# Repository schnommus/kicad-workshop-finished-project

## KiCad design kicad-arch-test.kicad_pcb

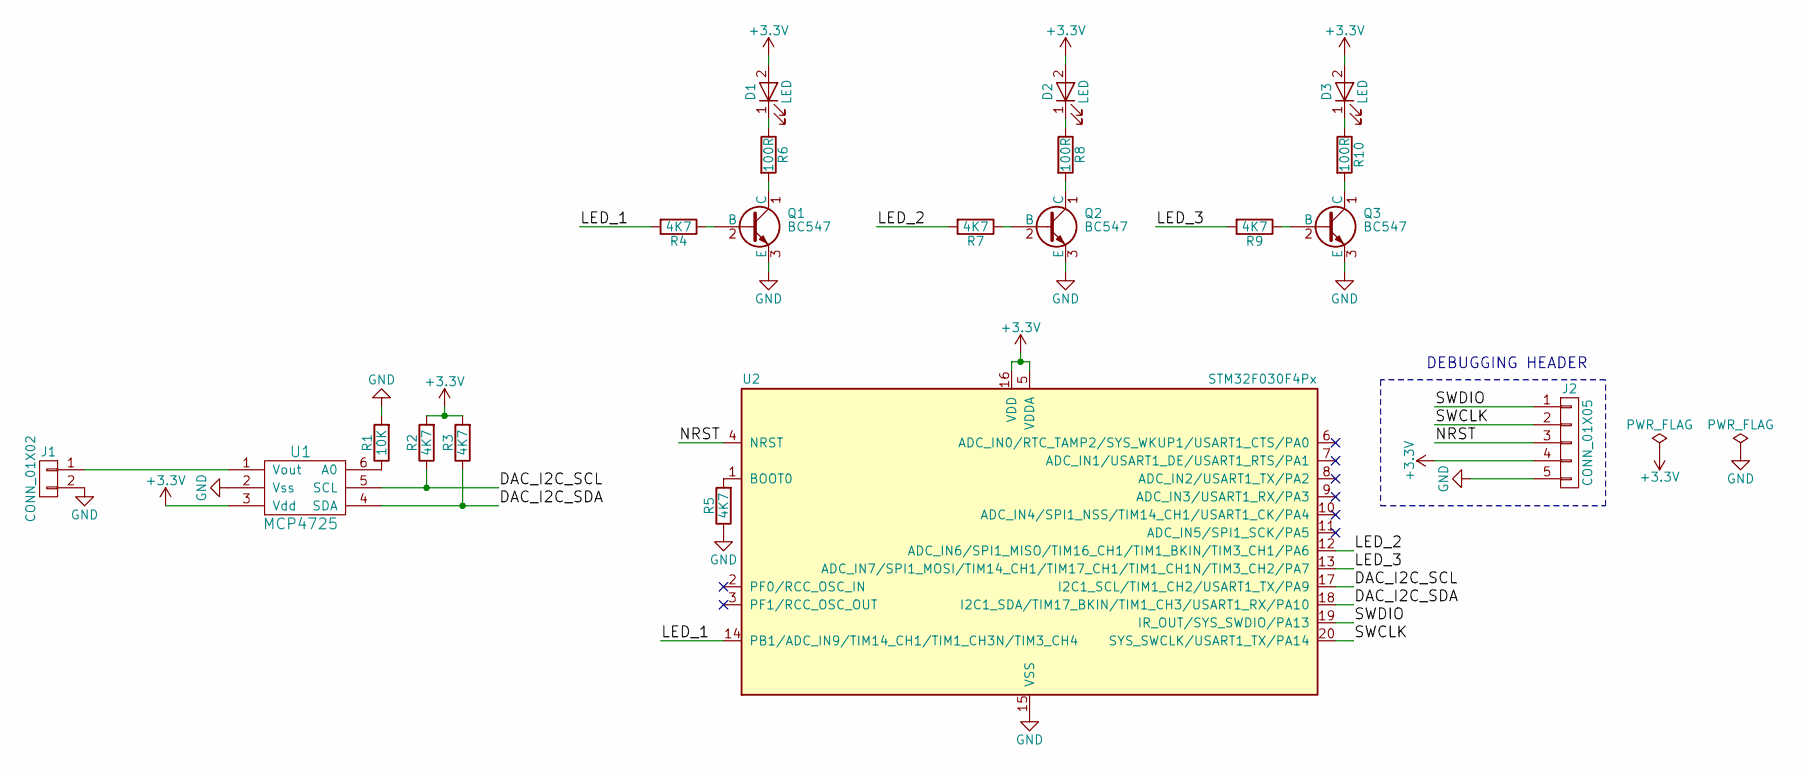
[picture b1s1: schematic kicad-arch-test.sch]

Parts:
D1, D2, D3: LED; LED_0805_HandSoldering
J1: CONN_01X02; Pin_Header_Straight_1x02_Pitch2.54mm
J2: CONN_01X05; Pin_Header_Straight_1x05_Pitch2.54mm
Q1, Q2, Q3: BC547; SOT-23W_Handsoldering
R1: 10K; R_0805_HandSoldering
R2, R3, R4, R5, R7, R9: 4K7; R_0805_HandSoldering
R6, R8, R10: 100R; R_0805_HandSoldering
U1: MCP4725; SOT-23-6_Handsoldering
U2: STM32F030F4Px; TSSOP-20_4.4x6.5mm_Pitch0.65mm

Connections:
+3V3: D1.2 (A), D2.2 (A), D3.2 (A), J2.4, R2.2, R3.2, U1.3 (Vdd), U2.5 (VDDA), U2.16 (VDD)
/DAC_I2C_SCL: R2.1, U1.5 (SCL), U2.17 (I2C1_SCL/TIM1_CH2/USART1_TX/PA9)
/DAC_I2C_SDA: R3.1, U1.4 (SDA), U2.18 (I2C1_SDA/TIM17_BKIN/TIM1_CH3/USART1_RX/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)
/LED_1: R4.2, U2.14 (PB1/ADC_IN9/TIM14_CH1/TIM1_CH3N/TIM3_CH4)
/LED_2: R7.2, U2.12 (ADC_IN6/SPI1_MISO/TIM16_CH1/TIM1_BKIN/T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)
/LED_3: R9.2, U2.13 (ADC_IN7/SPI1_MOSI/TIM14_CH1/TIM17_CH1/T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)
/NRST: J2.3, U2.4 (NRST)
/SWCLK: J2.2, U2.20 (SYS_SWCLK/USART1_TX/PA14)
/SWDIO: J2.1, U2.19 (IR_OUT/SYS_SWDIO/PA13)
GND: J1.2, J2.5, Q1.3 (E), Q2.3 (E), Q3.3 (E), R1.2, R5.1, U1.2 (Vss), U2.15 (VSS)
unnamed: D1.1 (K), R6.1
unnamed: D2.1 (K), R8.1
unnamed: D3.1 (K), R10.1
unnamed: J1.1, U1.1 (Vout)
unnamed: Q1.1 (C), R6.2
unnamed: Q1.2 (B), R4.1
unnamed: Q2.1 (C), R8.2
unnamed: Q2.2 (B), R7.1
unnamed: Q3.1 (C), R10.2
unnamed: Q3.2 (B), R9.1
unnamed: R1.1, U1.6 (A0)
unnamed: R5.2, U2.1 (BOOT0)

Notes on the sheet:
DEBUGGING HEADER

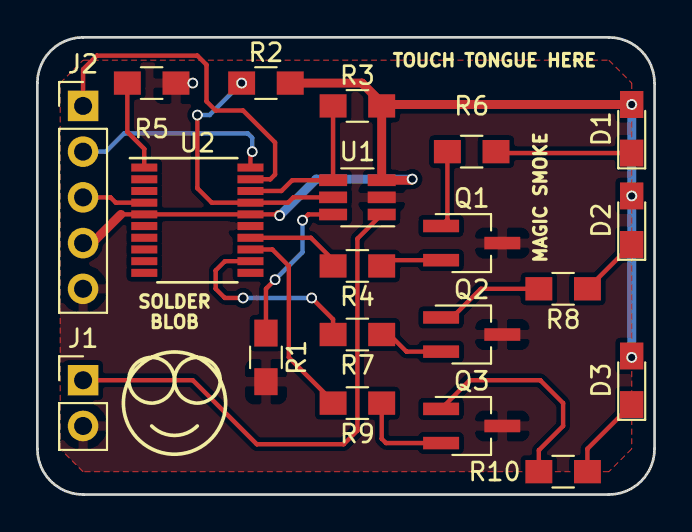
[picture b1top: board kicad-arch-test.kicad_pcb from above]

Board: 2 copper layers, 34.3 x 25.4 mm, 20 parts (0 on the bottom side), 22 nets.
